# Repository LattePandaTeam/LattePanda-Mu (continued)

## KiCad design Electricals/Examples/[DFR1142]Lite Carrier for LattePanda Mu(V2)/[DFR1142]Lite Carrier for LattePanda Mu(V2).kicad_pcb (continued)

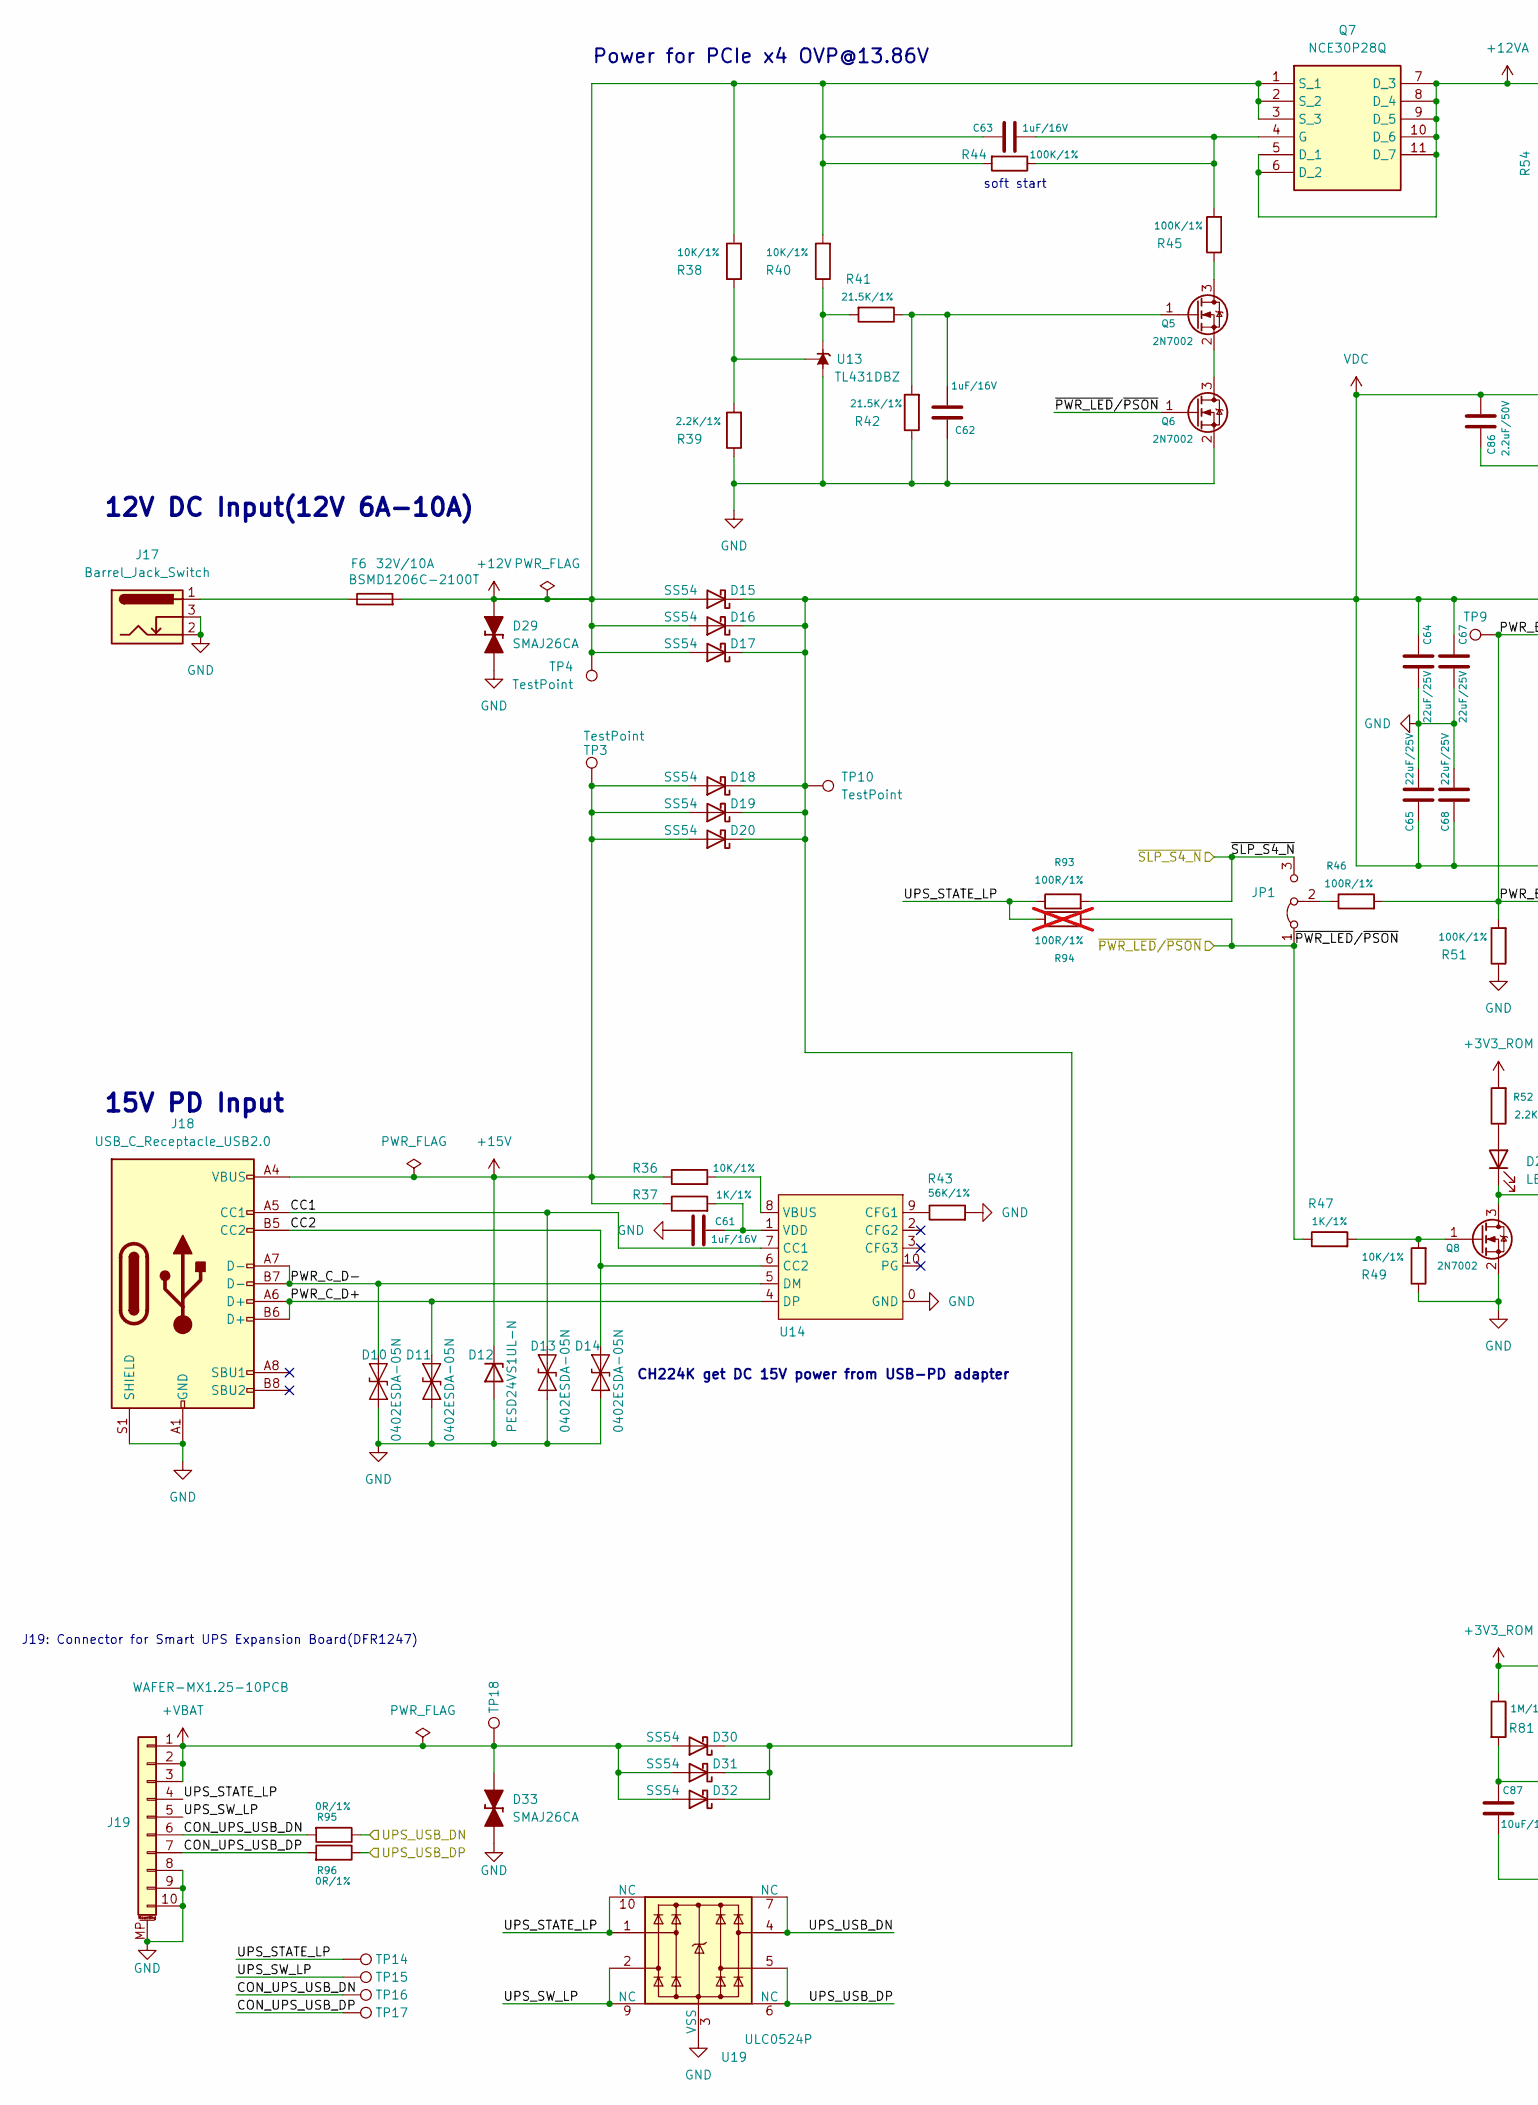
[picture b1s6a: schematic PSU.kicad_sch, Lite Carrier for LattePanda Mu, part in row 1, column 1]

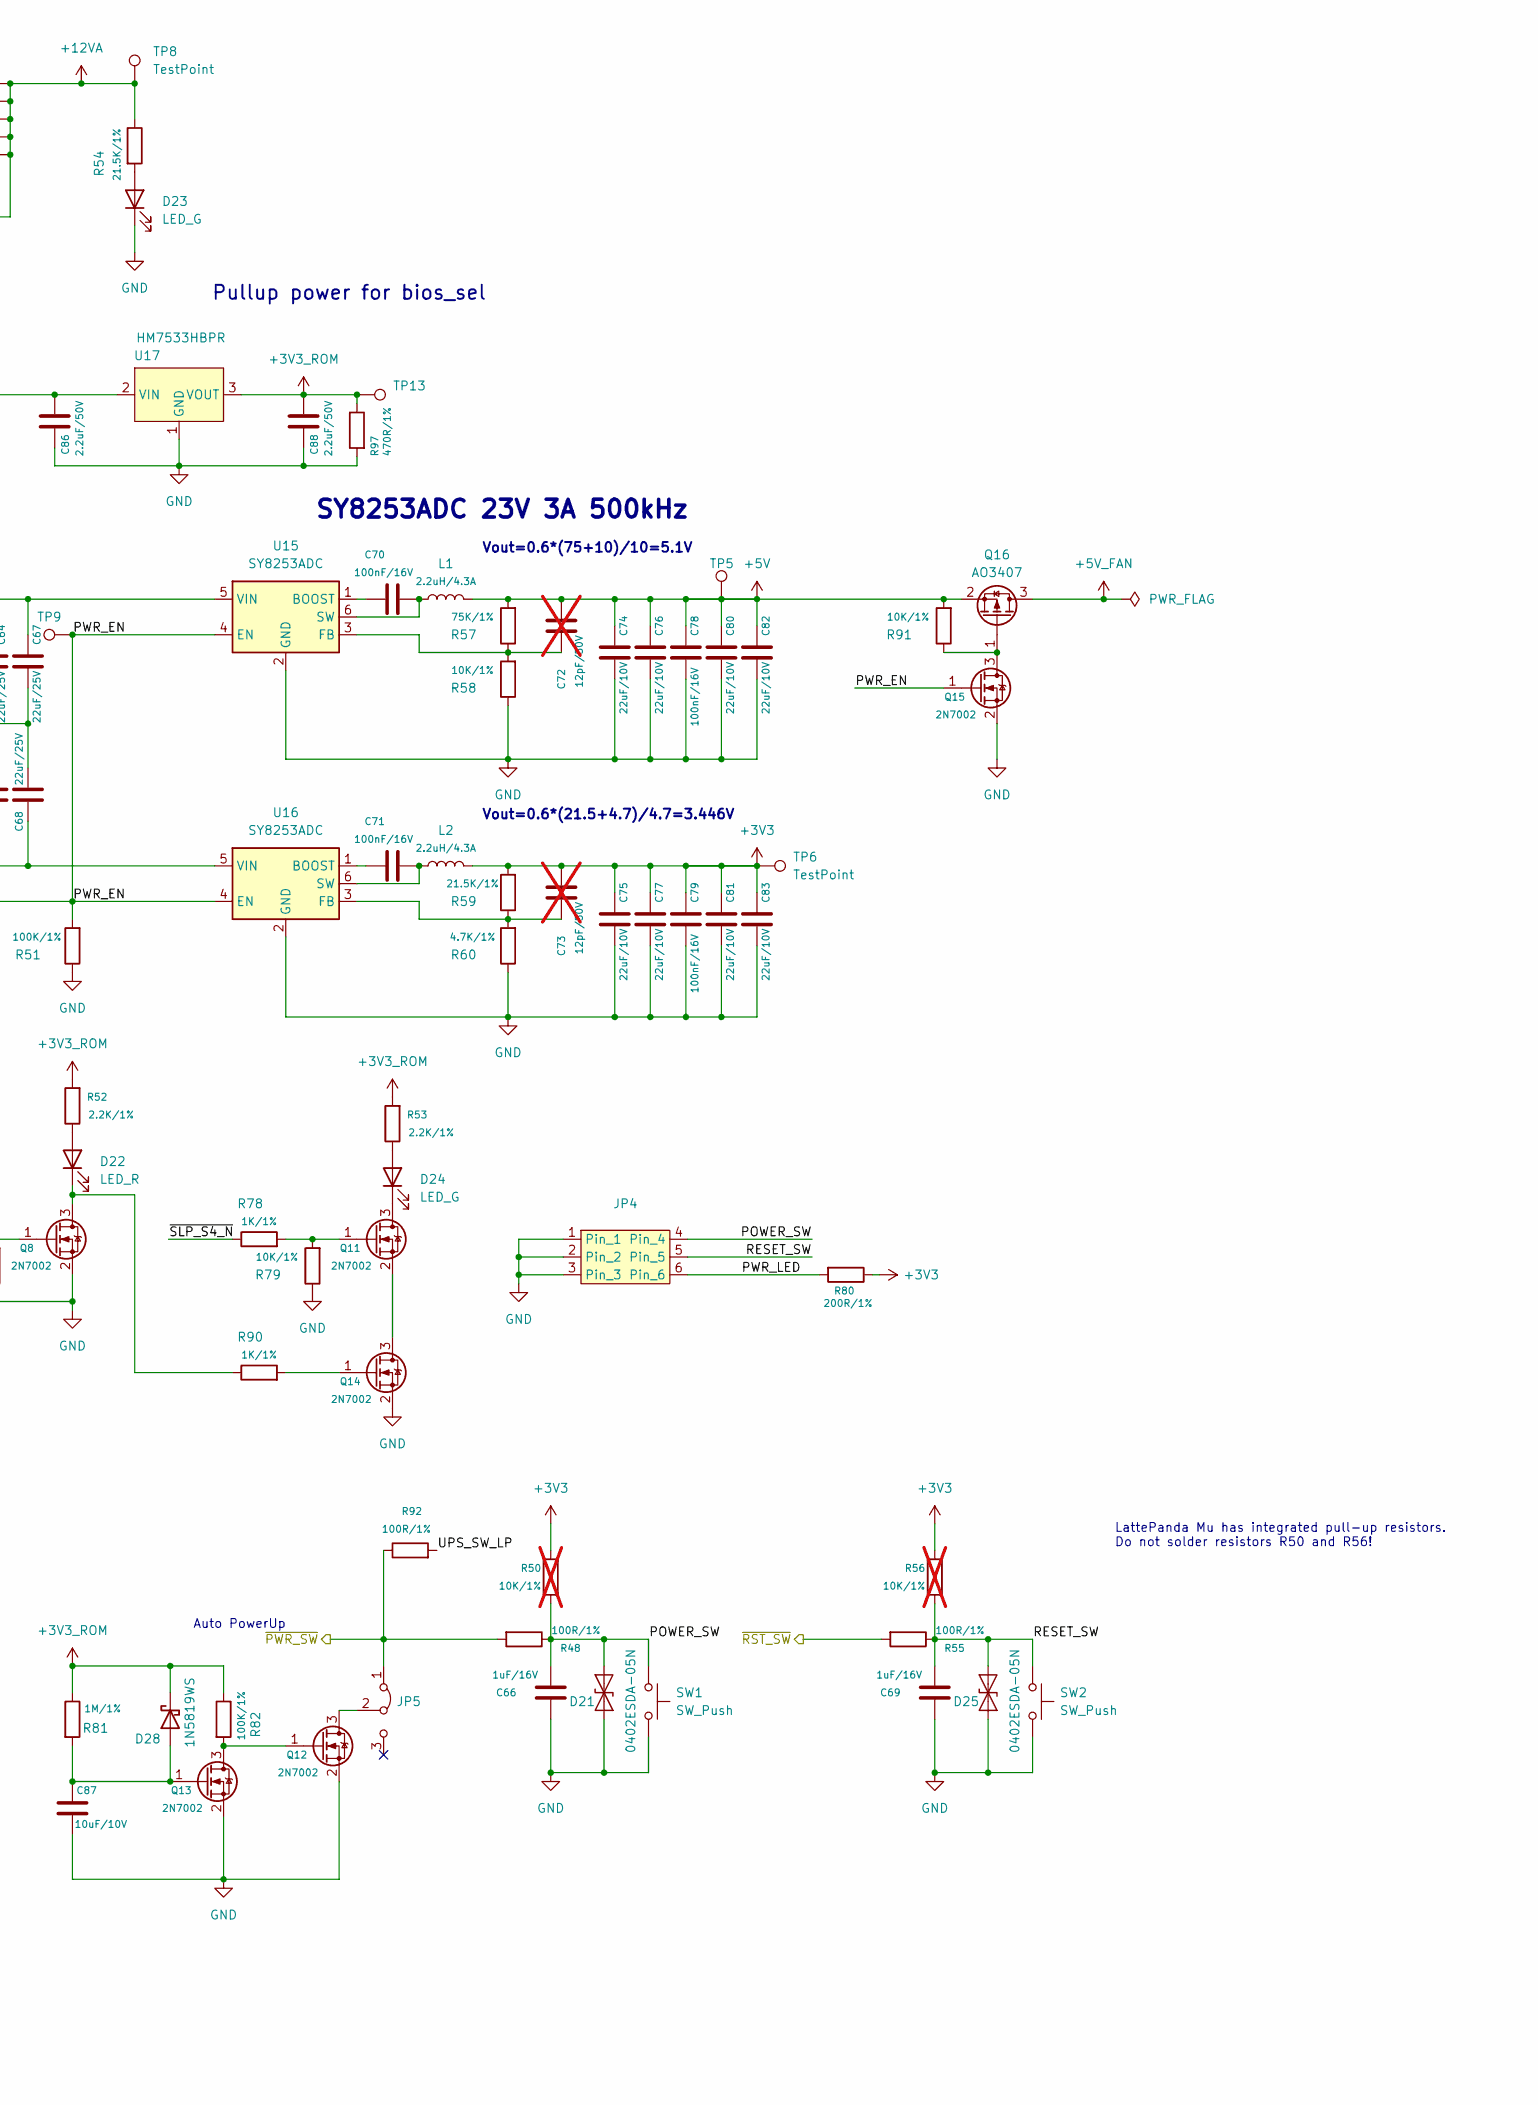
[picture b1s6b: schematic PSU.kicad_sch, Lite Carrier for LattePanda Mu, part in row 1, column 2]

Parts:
C61, C62, C63, C66, C69: 1uF/16V; C_0402_1005Metric
C64, C65, C67, C68: 22uF/25V; C_0805_2012Metric
C70, C71, C78, C79: 100nF/16V; C_0402_1005Metric
C72, C73: 12pF/50V; C_0402_1005Metric; not fitted
C74, C75, C76, C77, C80, C81, C82, C83: 22uF/10V; C_0603_1608Metric
C86, C88: 2.2uF/50V; C_0603
C87: 10uF/10V; C_0402_1005Metric
D10, D11, D13, D14, D21, D25: 0402ESDA-05N; D_0402_1005Metric
D12: PESD24VS1UL-N; D_0402_1005Metric
D15, D16, D17, D18, D19, D20, D30, D31, D32: SS54; D_SMA
D22: LED_R; LED_0603_1608Metric
D23, D24: LED_G; LED_0603_1608Metric
D28: 1N5819WS; D_SOD-323
D29, D33: SMAJ26CA; D_SMA
F6: BSMD1206C-2100T; R_1206
J17: Barrel_Jack_Switch; DC_Jack_DC007B_30V_10A
J18: USB_C_Receptacle_USB2.0; USB_C_Receptacle_G-Switch_GT-USB-7010ASV
J19: WAFER-MX1.25-10PCB; MX1.25-10P-SMD
JP1, JP5: Jumper_3_Bridged12; PinHeader_1x03_P2.54mm_Vertical
JP4: PinHeader_2x03_P2.54mm_Vertical
L1, L2: 2.2uH/4.3A; L_Sunlord_SWPA4020S
Q5, Q6, Q8, Q11, Q12, Q13, Q14, Q15: 2N7002; SOT-23
Q7: NCE30P28Q; MOSFET_PDFN8_3.3x3.3
Q16: AO3407; SOT-23
R36, R38, R40, R49, R58, R79, R91: 10K/1%; R_0402
R37, R47, R78, R90: 1K/1%; R_0402
R39, R52, R53: 2.2K/1%; R_0402
R41, R42, R54, R59: 21.5K/1%; R_0402
R43: 56K/1%; R_0402
R44, R45, R51, R82: 100K/1%; R_0402
R46, R48, R55, R92, R93: 100R/1%; R_0402
R50, R56: 10K/1%; R_0402_1005Metric; not fitted
R57: 75K/1%; R_0402
R60: 4.7K/1%; R_0402
R80: 200R/1%; R_0402
R81: 1M/1%; R_0402
R94: 100R/1%; R_0402; not fitted
R95, R96: 0R/1%; R_0402
R97: 470R/1%; R_0402
SW1, SW2: SW_Push; SW_PUSH_SIDE_TS-1012EV_7.7x3.95x3.5mm
TP3, TP4, TP5, TP6, TP8, TP9, TP10, TP13, TP14, TP15, TP16, TP17, TP18: TestPoint; TestPoint_Pad_D1.5mm
U13: TL431DBZ; SOT-23
U14: CH224K; ESSOP-10-1EP_3.9x5mm_P1.0mm_EP3.2x2.3
U15, U16: SY8253ADC; TSOT-23-6
U17: HM7533HBPR; SOT-89-3
U19: ULC0524P; Diodes_UDFN-10_1.0x2.5mm_P0.5mm

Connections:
+3V3: C73.1, C75.2, C77.2, C79.1, C81.2, C83.2, L2.2, R50.2, R56.2, R59.2, R80.1, TP6.1; also elsewhere on the board
+3V3_ROM: C88.1, D28.1 (K), R52.2, R53.2, R81.1, R82.1, R97.1, TP13.1, U17.3 (VOUT); also elsewhere on the board
+5V: C72.1, C74.2, C76.2, C78.1, C80.2, C82.2, L1.2, Q16.2 (S), R57.2, R91.2, TP5.1; also elsewhere on the board
+5V_FAN: Q16.3 (D); also elsewhere on the board
+12V: C63.2, D15.2 (A), D16.2 (A), D17.2 (A), D29.2 (A), F6.2, Q7.1 (S_1), Q7.2 (S_2), Q7.3 (S_3), R38.2, R40.2, R44.2, TP4.1
+12VA: Q7.5 (D_1), Q7.6 (D_2), Q7.7 (D_3), Q7.8 (D_4), Q7.9 (D_5), Q7.10 (D_6), Q7.11 (D_7), R54.1, TP8.1; also elsewhere on the board
+15V: D12.1 (K), D18.2 (A), D19.2 (A), D20.2 (A), J18.A4 (VBUS), J18.A9 (VBUS), J18.B4 (VBUS), J18.B9 (VBUS), R36.1, R37.1, TP3.1
+VBAT: D30.2 (A), D31.2 (A), D32.2 (A), D33.2 (A), J19.1, J19.2, J19.3, TP18.1
/LattePanda Module/~PWR_SW: JP5.1 (A), R48.2, R92.1; also elsewhere on the board
/LattePanda Module/~RST_SW: R55.2; also elsewhere on the board
/PSU/CC1: D13.2 (A2), J18.A5 (CC1), U14.7 (CC1)
/PSU/CC2: D14.2 (A2), J18.B5 (CC2), U14.6 (CC2)
/PSU/CON_UPS_USB_DN: J19.6, R95.2, TP16.1
/PSU/CON_UPS_USB_DP: J19.7, R96.2, TP17.1
/PSU/POWER_SW: C66.1, D21.2 (A2), JP4.4, R48.1, R50.1, SW1.1
/PSU/PWR_C_D+: D11.2 (A2), J18.A6 (D+), J18.B6 (D+), U14.4 (DP)
/PSU/PWR_C_D-: D10.2 (A2), J18.A7 (D-), J18.B7 (D-), U14.5 (DM)
/PSU/PWR_EN: Q15.1 (G), R46.2, R51.2, TP9.1, U15.4 (EN), U16.4 (EN)
/PSU/PWR_LED: JP4.6, R80.2
/PSU/RESET_SW: C69.1, D25.2 (A2), JP4.5, R55.1, R56.1, SW2.1
/PSU/UPS_STATE_LP: J19.4, R93.1, R94.1, TP14.1, U19.1, U19.10 (NC)
/PSU/UPS_SW_LP: J19.5, R92.2, TP15.1, U19.2, U19.9 (NC)
/PSU/UPS_USB_DN: R95.1; also elsewhere on the board
/PSU/UPS_USB_DP: R96.1; also elsewhere on the board
/PSU/~SLP_S4_N: JP1.3 (B), R78.1, R93.2; also elsewhere on the board
/~PWR_LED/~PSON: JP1.1 (A), Q6.1 (G), R47.1, R94.2; also elsewhere on the board
GND: C61.2, C62.2, C64.1, C65.1, C66.2, C67.1, C68.1, C69.2, C74.1, C75.1, C76.1, C77.1, C78.2, C79.2, C80.1, C81.1, C82.1, C83.1, C86.2, C87.2, C88.2, D10.1 (A1), D11.1 (A1), D12.2 (A), D13.1 (A1), D14.1 (A1), D21.1 (A1), D23.1 (K), D25.1 (A1), D29.1 (K), D33.1 (K), J17.2, J17.3, J18.A1 (GND), J18.A12 (GND), J18.B1 (GND), J18.B12 (GND), J18.S1 (SHIELD), J19.8, J19.9, J19.10, J19.MP (MountPin), JP4.1, JP4.2, JP4.3, Q6.2 (S), Q8.2 (S), Q12.2 (S), Q13.2 (S), Q14.2 (S), Q15.2 (S), R39.1, R42.1, R43.2, R49.1, R51.1, R58.1, R60.1, R79.1, R97.2, SW1.2, SW2.2, U13.3 (A), U14.0 (GND), U15.2 (GND), U16.2 (GND), U17.1 (GND), U19.3 (VSS), U19.8 (VSS); also elsewhere on the board
unnamed: D22.2 (A), R52.1
unnamed: D22.1 (K), Q8.3 (D), R90.1
unnamed: D23.2 (A), R54.2
unnamed: D24.2 (A), R53.1
unnamed: D24.1 (K), Q11.3 (D)
unnamed: C87.1, D28.2 (A), Q13.1 (G), R81.2
unnamed: F6.1, J17.1
unnamed: JP1.2 (C), R46.1
unnamed: JP5.2 (C), Q12.3 (D)
unnamed: Q5.3 (D), R45.1
unnamed: C62.1, Q5.1 (G), R41.1, R42.2
unnamed: Q5.2 (S), Q6.3 (D)
unnamed: C63.1, Q7.4 (G), R44.1, R45.2
unnamed: Q8.1 (G), R47.2, R49.2
unnamed: Q11.1 (G), R78.2, R79.2
unnamed: Q11.2 (S), Q14.3 (D)
unnamed: Q12.1 (G), Q13.3 (D), R82.2
unnamed: Q14.1 (G), R90.2
unnamed: Q15.3 (D), Q16.1 (G), R91.1
unnamed: R40.1, R41.2, U13.1 (K)
unnamed: R38.1, R39.2, U13.2 (REF)
unnamed: R43.1, U14.9 (CFG1)
unnamed: R36.2, U14.8 (VBUS)
unnamed: C61.1, R37.2, U14.1 (VDD)
unnamed: C70.2, U15.1 (BOOST)
unnamed: C72.2, R57.1, R58.2, U15.3 (FB)
unnamed: C70.1, L1.1, U15.6 (SW)
unnamed: C71.2, U16.1 (BOOST)
unnamed: C73.2, R59.1, R60.2, U16.3 (FB)
unnamed: C71.1, L2.1, U16.6 (SW)
unnamed: U19.4, U19.7 (NC)
unnamed: U19.5, U19.6 (NC)
VDC: C64.2, C65.2, C67.2, C68.2, C86.1, D15.1 (K), D16.1 (K), D17.1 (K), D18.1 (K), D19.1 (K), D20.1 (K), D30.1 (K), D31.1 (K), D32.1 (K), TP10.1, U15.5 (VIN), U16.5 (VIN), U17.2 (VIN); also elsewhere on the board

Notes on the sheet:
soft start
15V PD Input
J19: Connector for Smart UPS Expansion Board(DFR1247)
SY8253ADC 23V 3A 500kHz
Auto PowerUp
Power for PCIe x4 OVP@13.86V
Vout=0.6*(75+10)/10=5.1V
LattePanda Mu has integrated pull-up resistors. Do not solder resistors R50 and R56!
12V DC Input(12V 6A-10A)
CH224K get DC 15V power from USB-PD adapter
Pullup power for bios_sel
Vout=0.6*(21.5+4.7)/4.7=3.446V

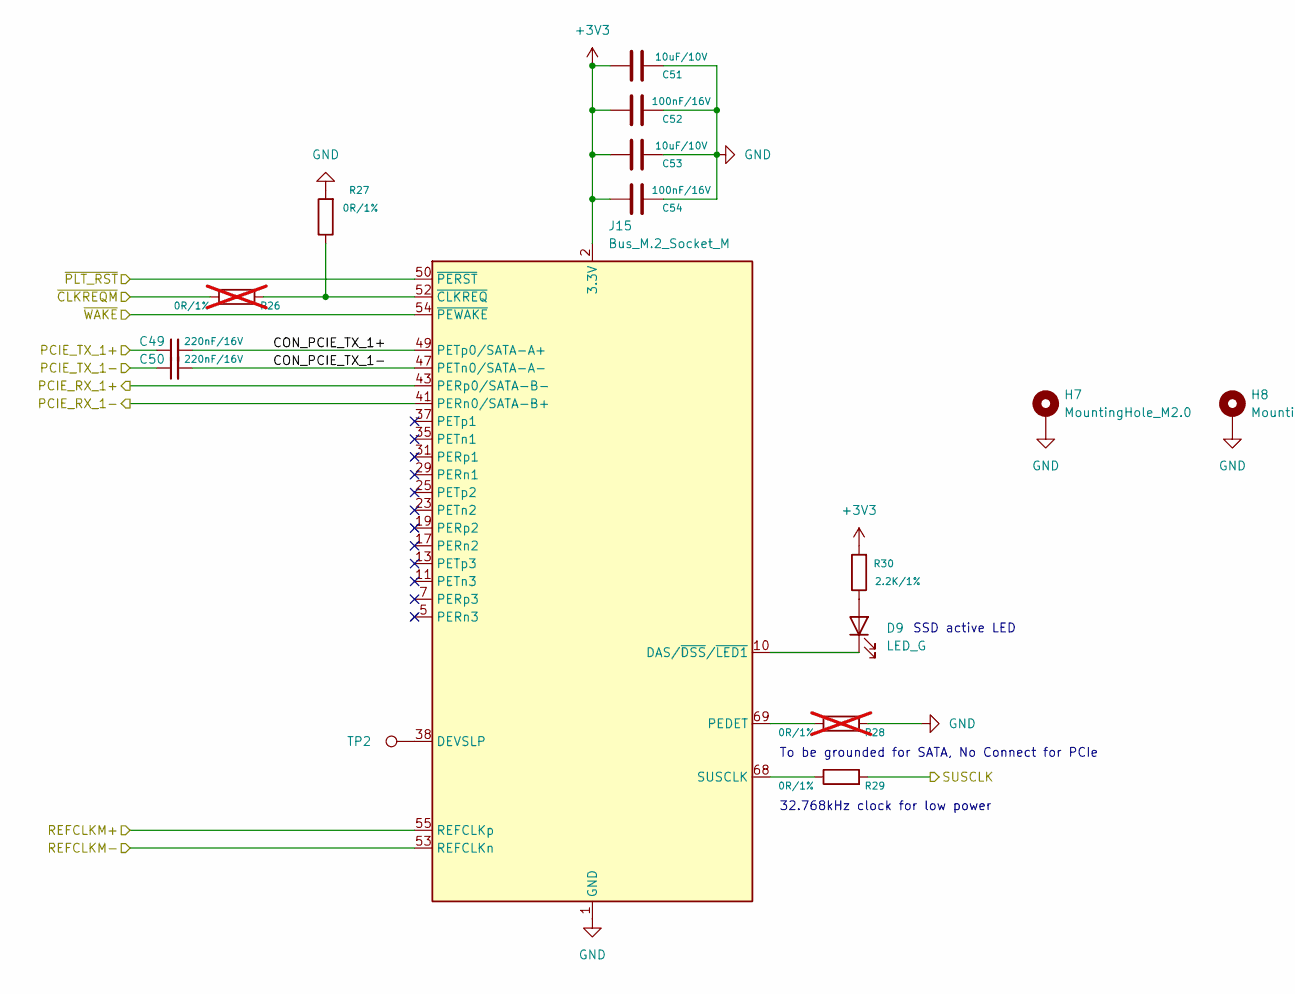
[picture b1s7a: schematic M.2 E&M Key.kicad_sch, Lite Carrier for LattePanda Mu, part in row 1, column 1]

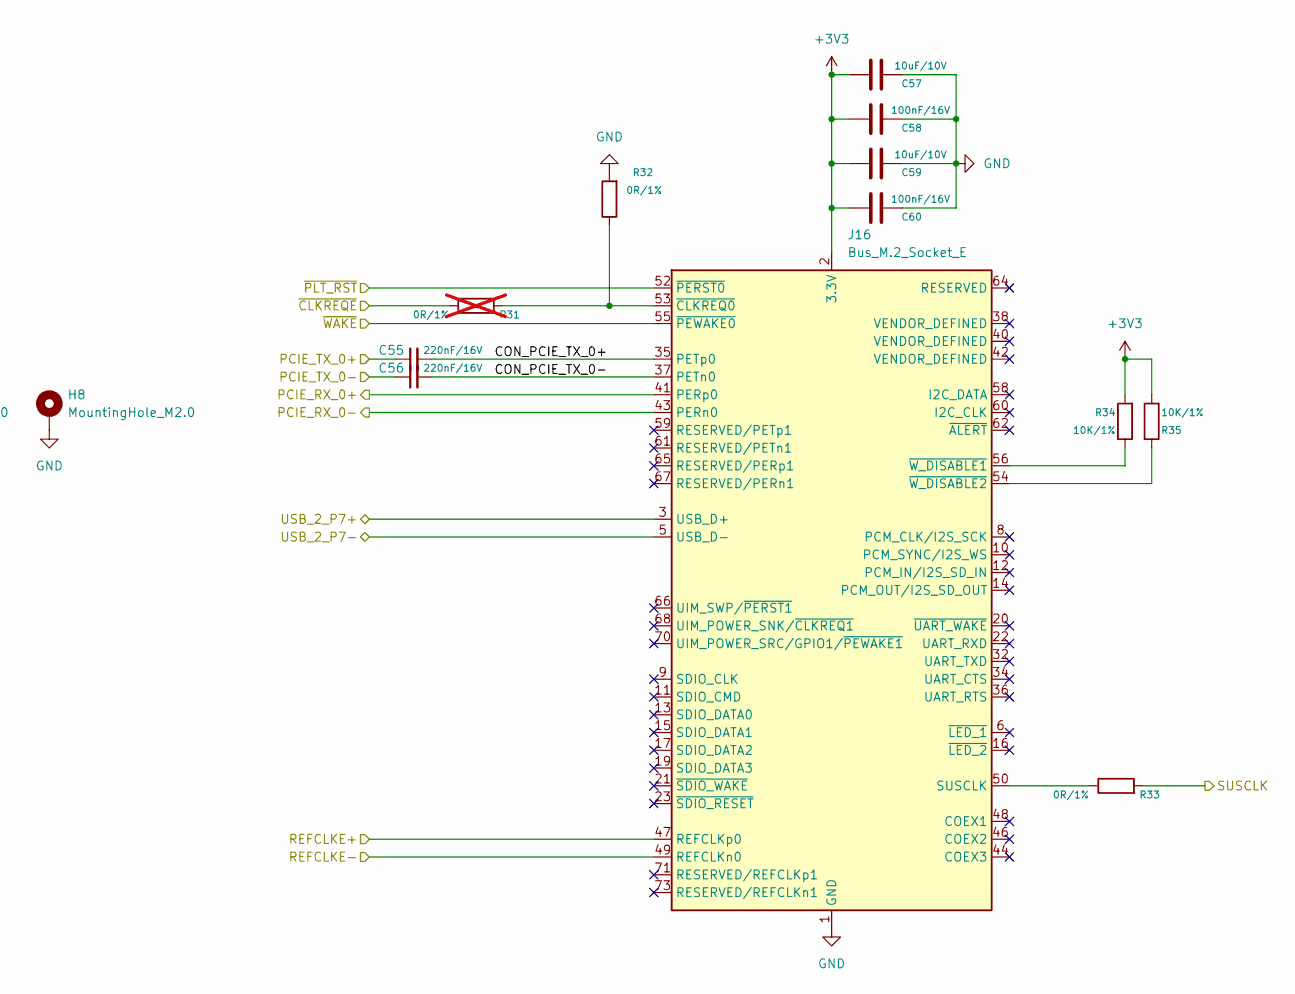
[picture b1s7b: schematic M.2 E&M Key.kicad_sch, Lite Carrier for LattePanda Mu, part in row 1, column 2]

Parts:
C49, C50, C55, C56: 220nF/16V; C_0402_1005Metric
C51, C53, C57, C59: 10uF/10V; C_0402_1005Metric
C52, C54, C58, C60: 100nF/16V; C_0402_1005Metric
D9: LED_G; LED_0603_1608Metric
H7, H8: MountingHole_M2.0; MountingHole_2.75mm_M2_4.4mm_Pad_TopOnly
J15: Bus_M.2_Socket_M; PCIe_M.2_Connectors_P=0.5mm_H=4.2mm_KeyM
J16: Bus_M.2_Socket_E; PCIe_M.2_Connectors_P=0.5mm_H=4.2mm_KeyE
R26, R28, R31: 0R/1%; R_0402_1005Metric; not fitted
R27, R29, R32, R33: 0R/1%; R_0402
R30: 2.2K/1%; R_0402
R34, R35: 10K/1%; R_0402
TP2: TestPoint; TestPoint_Pad_D1.5mm

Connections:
+3V3: C51.2, C52.2, C53.2, C54.2, C57.2, C58.2, C59.2, C60.2, J15.2 (3.3V), J15.4 (3.3V), J15.12 (3.3V), J15.14 (3.3V), J15.16 (3.3V), J15.18 (3.3V), J15.70 (3.3V), J15.72 (3.3V), J15.74 (3.3V), J16.2 (3.3V), J16.4 (3.3V), J16.72 (3.3V), J16.74 (3.3V), R30.2, R34.2, R35.1; also elsewhere on the board
/LattePanda Module/HSIO_2_RX+: J15.43 (PERp0/SATA-B-); also elsewhere on the board
/LattePanda Module/HSIO_2_RX-: J15.41 (PERn0/SATA-B+); also elsewhere on the board
/LattePanda Module/HSIO_2_TX+: C49.1; also elsewhere on the board
/LattePanda Module/HSIO_2_TX-: C50.1; also elsewhere on the board
/LattePanda Module/HSIO_3_RX+: J16.41 (PERp0); also elsewhere on the board
/LattePanda Module/HSIO_3_RX-: J16.43 (PERn0); also elsewhere on the board
/LattePanda Module/HSIO_3_TX+: C55.1; also elsewhere on the board
/LattePanda Module/HSIO_3_TX-: C56.1; also elsewhere on the board
/LattePanda Module/REFCLK0+: J15.53 (REFCLKn); also elsewhere on the board
/LattePanda Module/REFCLK0-: J15.55 (REFCLKp); also elsewhere on the board
/LattePanda Module/REFCLK3+: J16.47 (REFCLKp0); also elsewhere on the board
/LattePanda Module/REFCLK3-: J16.49 (REFCLKn0); also elsewhere on the board
/LattePanda Module/SUSCLK_WIFI: R29.2, R33.2; also elsewhere on the board
/LattePanda Module/USB_2_P7+: J16.3 (USB_D+); also elsewhere on the board
/LattePanda Module/USB_2_P7-: J16.5 (USB_D-); also elsewhere on the board
/LattePanda Module/~CLKREQ3: R31.1; also elsewhere on the board
/M.2 E&M Key/CON_PCIE_TX_0+: C55.2, J16.35 (PETp0)
/M.2 E&M Key/CON_PCIE_TX_0-: C56.2, J16.37 (PETn0)
/M.2 E&M Key/CON_PCIE_TX_1+: C49.2, J15.49 (PETp0/SATA-A+)
/M.2 E&M Key/CON_PCIE_TX_1-: C50.2, J15.47 (PETn0/SATA-A-)
/M.2 E&M Key/~CLKREQM: R26.1
/~PLT_RST: J15.50 (~PERST), J16.52 (~PERST0); also elsewhere on the board
/~WAKE: J15.54 (~PEWAKE), J16.55 (~PEWAKE0); also elsewhere on the board
GND: C51.1, C52.1, C53.1, C54.1, C57.1, C58.1, C59.1, C60.1, H7.1, H8.1, J15.1 (GND), J15.3 (GND), J15.9 (GND), J15.15 (GND), J15.21 (GND), J15.27 (GND), J15.33 (GND), J15.39 (GND), J15.45 (GND), J15.51 (GND), J15.57 (GND), J15.71 (GND), J15.73 (GND), J15.75 (GND), J15.MP1, J15.MP2, J16.1 (GND), J16.7 (GND), J16.18 (GND), J16.33 (GND), J16.39 (GND), J16.45 (GND), J16.51 (GND), J16.57 (GND), J16.63 (GND), J16.69 (GND), J16.75 (GND), J16.MP1, J16.MP2, R27.2, R28.2, R32.2; also elsewhere on the board
unnamed: D9.2 (A), R30.1
unnamed: D9.1 (K), J15.10 (DAS/~DSS/~LED1)
unnamed: J15.38 (DEVSLP), TP2.1
unnamed: J15.69 (PEDET), R28.1
unnamed: J15.68 (SUSCLK), R29.1
unnamed: J15.52 (~CLKREQ), R26.2, R27.1
unnamed: J16.50 (SUSCLK), R33.1
unnamed: J16.53 (~CLKREQ0), R31.2, R32.1
unnamed: J16.56 (~W_DISABLE1), R34.1
unnamed: J16.54 (~W_DISABLE2), R35.2

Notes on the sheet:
To be grounded for SATA, No Connect for PCIe
SSD active LED
32.768kHz clock for low power

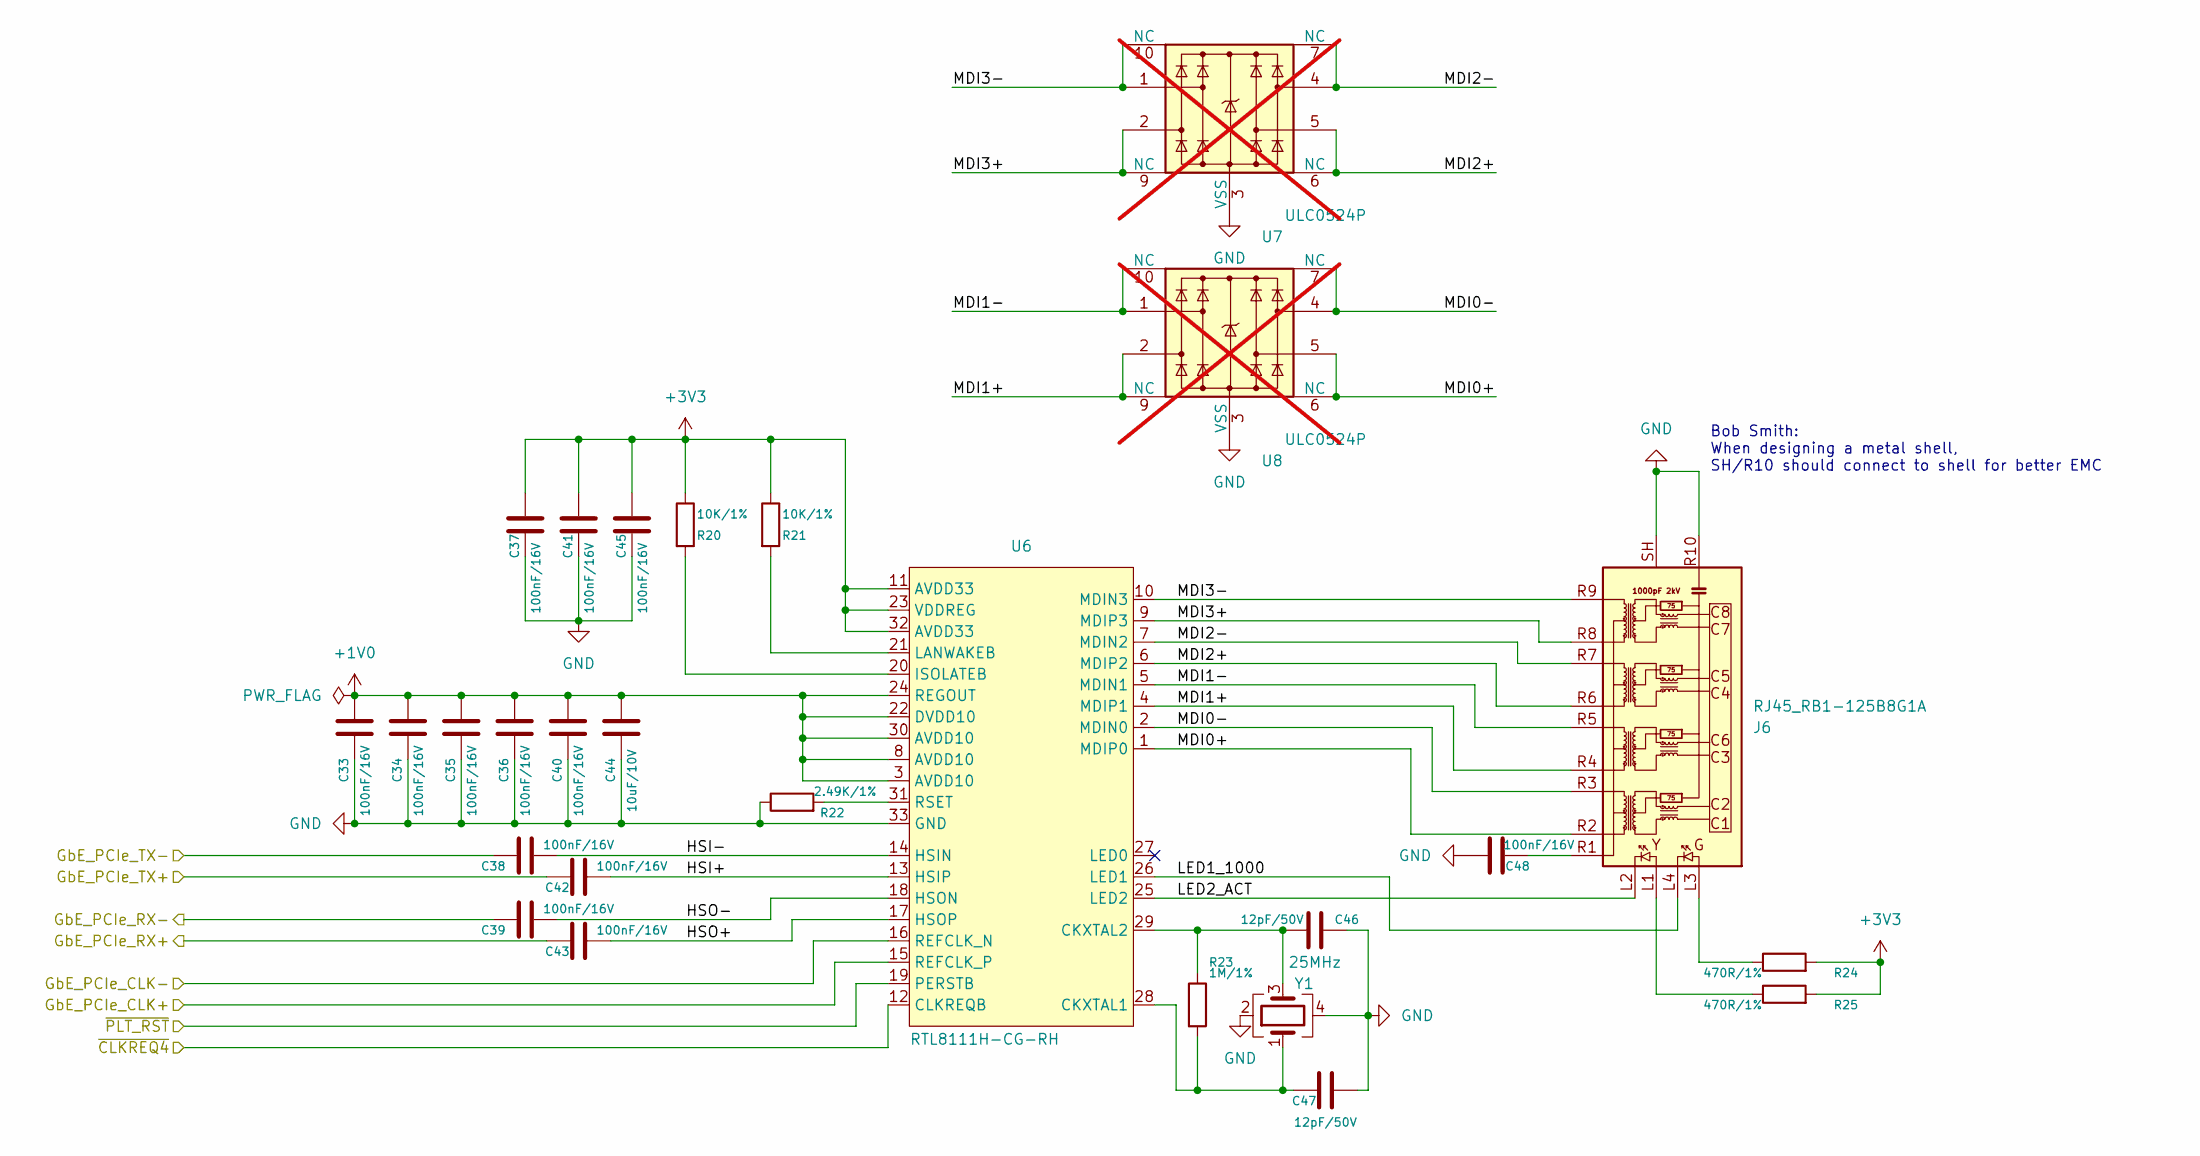
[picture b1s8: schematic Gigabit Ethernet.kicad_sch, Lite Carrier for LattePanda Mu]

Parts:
C33, C34, C35, C36, C37, C38, C39, C40, C41, C42, C43, C45, C48: 100nF/16V; C_0402_1005Metric
C44: 10uF/10V; C_0402_1005Metric
C46, C47: 12pF/50V; C_0402_1005Metric
J6: RJ45_RB1-125B8G1A; RJ45_UDE_RB1-125B8G1A
R20, R21: 10K/1%; R_0402
R22: 2.49K/1%; R_0603_1608Metric
R23: 1M/1%; R_0402
R24, R25: 470R/1%; R_0402
U6: RTL8111H-CG-RH; QFN-32-1EP_4x4mm_P0.4mm_EP2.65x2.65mm
U7, U8: ULC0524P; Diodes_UDFN-10_1.0x2.5mm_P0.5mm; not fitted
Y1: 25MHz; Crystal_SMD_3225-4Pin_3.2x2.5mm

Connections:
+1V0: C33.2, C34.2, C35.2, C36.2, C40.2, C44.2, U6.3 (AVDD10), U6.8 (AVDD10), U6.22 (DVDD10), U6.24 (REGOUT), U6.30 (AVDD10)
+3V3: C37.2, C41.2, C45.2, R20.1, R21.1, R24.2, R25.2, U6.11 (AVDD33), U6.23 (VDDREG), U6.32 (AVDD33); also elsewhere on the board
/Gigabit Ethernet/GbE_PCIe_CLK+: U6.15 (REFCLK_P); also elsewhere on the board
/Gigabit Ethernet/GbE_PCIe_CLK-: U6.16 (REFCLK_N); also elsewhere on the board
/Gigabit Ethernet/GbE_PCIe_RX+: C43.2; also elsewhere on the board
/Gigabit Ethernet/GbE_PCIe_RX-: C39.2; also elsewhere on the board
/Gigabit Ethernet/GbE_PCIe_TX+: C42.2; also elsewhere on the board
/Gigabit Ethernet/GbE_PCIe_TX-: C38.2; also elsewhere on the board
/Gigabit Ethernet/HSI+: C42.1, U6.13 (HSIP)
/Gigabit Ethernet/HSI-: C38.1, U6.14 (HSIN)
/Gigabit Ethernet/HSO+: C43.1, U6.17 (HSOP)
/Gigabit Ethernet/HSO-: C39.1, U6.18 (HSON)
/Gigabit Ethernet/LED0_100: U6.27 (LED0)
/Gigabit Ethernet/LED1_1000: J6.L4, U6.26 (LED1)
/Gigabit Ethernet/LED2_ACT: J6.L2, U6.25 (LED2)
/Gigabit Ethernet/MDI0+: J6.R2 (TD1+), U6.1 (MDIP0), U8.5, U8.6 (NC)
/Gigabit Ethernet/MDI0-: J6.R3 (TD1-), U6.2 (MDIN0), U8.4, U8.7 (NC)
/Gigabit Ethernet/MDI1+: J6.R4 (TD2+), U6.4 (MDIP1), U8.2, U8.9 (NC)
/Gigabit Ethernet/MDI1-: J6.R5 (TD2-), U6.5 (MDIN1), U8.1, U8.10 (NC)
/Gigabit Ethernet/MDI2+: J6.R6 (TD3+), U6.6 (MDIP2), U7.5, U7.6 (NC)
/Gigabit Ethernet/MDI2-: J6.R7 (TD3-), U6.7 (MDIN2), U7.4, U7.7 (NC)
/Gigabit Ethernet/MDI3+: J6.R8 (TD4+), U6.9 (MDIP3), U7.2, U7.9 (NC)
/Gigabit Ethernet/MDI3-: J6.R9 (TD4-), U6.10 (MDIN3), U7.1, U7.10 (NC)
/Gigabit Ethernet/~CLKREQ4: U6.12 (CLKREQB); also elsewhere on the board
/~PLT_RST: U6.19 (PERSTB); also elsewhere on the board
GND: C33.1, C34.1, C35.1, C36.1, C37.1, C40.1, C41.1, C44.1, C45.1, C46.1, C47.1, C48.2, J6.R10 (GND), J6.SH, R22.1, U6.33 (GND), U7.3 (VSS), U7.8 (VSS), U8.3 (VSS), U8.8 (VSS), Y1.2, Y1.4; also elsewhere on the board
unnamed: C48.1, J6.R1 (CT)
unnamed: J6.L1, R25.1
unnamed: J6.L3, R24.1
unnamed: C47.2, R23.2, U6.28 (CKXTAL1), Y1.1
unnamed: C46.2, R23.1, U6.29 (CKXTAL2), Y1.3
unnamed: R20.2, U6.20 (ISOLATEB)
unnamed: R21.2, U6.21 (LANWAKEB)
unnamed: R22.2, U6.31 (RSET)

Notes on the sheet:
Bob Smith: When designing a metal shell, SH/R10 should connect to shell for better EMC

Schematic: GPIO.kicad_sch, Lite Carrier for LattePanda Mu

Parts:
J7, J9, J12, J13: Conn_01x04_Pin; PinHeader_1x04_P2.54mm_Vertical
J8, J10, J11, J14: Conn_01x03_Pin; PinHeader_1x03_P2.54mm_Vertical
U9, U10, U11, U12: ULC0524P; Diodes_UDFN-10_1.0x2.5mm_P0.5mm

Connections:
+3V3: J13.1, J13.2, J13.3, J13.4, J14.1, J14.2, J14.3; also elsewhere on the board
/GPIO/I2C2_SCL: J9.1, U11.1, U11.10 (NC); also elsewhere on the board
/GPIO/I2C2_SDA: J7.1, U9.1, U9.10 (NC); also elsewhere on the board
/GPIO/I2C3_SCL: J9.2, U11.2, U11.9 (NC); also elsewhere on the board
/GPIO/I2C3_SDA: J7.2, U9.2, U9.9 (NC); also elsewhere on the board
/GPIO/I2C4_SCL: J9.3, U11.4, U11.7 (NC); also elsewhere on the board
/GPIO/I2C4_SDA: J7.3, U9.4, U9.7 (NC); also elsewhere on the board
/GPIO/I2C5_SCL: J9.4, U11.5, U11.6 (NC); also elsewhere on the board
/GPIO/I2C5_SDA: J7.4, U9.5, U9.6 (NC); also elsewhere on the board
/GPIO/SOC_UART0_RX: J8.1, U10.1, U10.10 (NC); also elsewhere on the board
/GPIO/SOC_UART0_TX: J10.1, U12.1, U12.10 (NC); also elsewhere on the board
/GPIO/SOC_UART1_RX: J8.2, U10.2, U10.9 (NC); also elsewhere on the board
/GPIO/SOC_UART1_TX: J10.2, U12.2, U12.9 (NC); also elsewhere on the board
/GPIO/SOC_UART2_RX: J8.3, U10.4, U10.7 (NC); also elsewhere on the board
/GPIO/SOC_UART2_TX: J10.3, U12.4, U12.7 (NC); also elsewhere on the board
GND: J11.1, J11.2, J11.3, J12.1, J12.2, J12.3, J12.4, U9.3 (VSS), U9.8 (VSS), U10.3 (VSS), U10.8 (VSS), U11.3 (VSS), U11.8 (VSS), U12.3 (VSS), U12.8 (VSS); also elsewhere on the board
unnamed: U10.5, U10.6 (NC)
unnamed: U12.5, U12.6 (NC)

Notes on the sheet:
I2C have internal 2.2k resistor pull-up to 3V3 on LattePanda Mu compute module.

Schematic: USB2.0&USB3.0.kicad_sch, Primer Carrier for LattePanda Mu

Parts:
C26, C27, C28, C29: 100nF/16V; C_0402_1005Metric
C30, C31, C32: 22uF/10V; C_0603_1608Metric
D5, D6, D7, D8: 0402ESDA-05N; D_0402_1005Metric
F2, F3: 6V/1A; Fuse_0805_2012Metric
F4, F5: 6V/2A; Fuse_0805_2012Metric
J4: USB3_A_Stacked; USB3_A_Molex_48406-0001_Horizontal_Stacked
J5: USB_A_Stacked; USB_A_CUI_UJ2-ADH-TH_Horizontal_Stacked
U3, U4, U5: ULC0524P; Diodes_UDFN-10_1.0x2.5mm_P0.5mm

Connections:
+5V: C30.2, C31.2, C32.2, F2.1, F3.1, F4.1, F5.1; also elsewhere on the board
/LattePanda Module/HSIO_0_TX+: C27.1; also elsewhere on the board
/LattePanda Module/HSIO_0_TX-: C26.1; also elsewhere on the board
/LattePanda Module/HSIO_1_TX+: C29.1; also elsewhere on the board
/LattePanda Module/HSIO_1_TX-: C28.1; also elsewhere on the board
/USB2.0&USB3.0/CON_USB1_D_N: J5.2 (D1-), U4.2, U4.9 (NC); also elsewhere on the board
/USB2.0&USB3.0/CON_USB1_D_P: J5.3 (D1+), U4.1, U4.10 (NC); also elsewhere on the board
/USB2.0&USB3.0/CON_USB2_D_N: J5.6 (D2-), U4.5, U4.6 (NC); also elsewhere on the board
/USB2.0&USB3.0/CON_USB2_D_P: J5.7 (D2+), U4.4, U4.7 (NC); also elsewhere on the board
/USB2.0&USB3.0/CON_USB3_D_N: D8.2 (A2), J4.2 (D1-); also elsewhere on the board
/USB2.0&USB3.0/CON_USB3_D_P: D7.2 (A2), J4.3 (D1+); also elsewhere on the board
/USB2.0&USB3.0/CON_USB3_SSRX_N: J4.5 (SSRX1-), U5.4, U5.7 (NC); also elsewhere on the board
/USB2.0&USB3.0/CON_USB3_SSRX_P: J4.6 (SSRX1+), U5.5, U5.6 (NC); also elsewhere on the board
/USB2.0&USB3.0/CON_USB3_SSTX_N: C26.2, J4.8 (SSTX1-), U3.4, U3.7 (NC)
/USB2.0&USB3.0/CON_USB3_SSTX_P: C27.2, J4.9 (SSTX1+), U3.5, U3.6 (NC)
/USB2.0&USB3.0/CON_USB4_D_N: D6.2 (A2), J4.11 (D2-); also elsewhere on the board
/USB2.0&USB3.0/CON_USB4_D_P: D5.2 (A2), J4.12 (D2+); also elsewhere on the board
/USB2.0&USB3.0/CON_USB4_SSRX_N: J4.14 (SSRX2-), U5.1, U5.10 (NC); also elsewhere on the board
/USB2.0&USB3.0/CON_USB4_SSRX_P: J4.15 (SSRX2+), U5.2, U5.9 (NC); also elsewhere on the board
/USB2.0&USB3.0/CON_USB4_SSTX_N: C28.2, J4.17 (SSTX2-), U3.1, U3.10 (NC)
/USB2.0&USB3.0/CON_USB4_SSTX_P: C29.2, J4.18 (SSTX2+), U3.2, U3.9 (NC)
GND: C30.1, C31.1, C32.1, D5.1 (A1), D6.1 (A1), D7.1 (A1), D8.1 (A1), J4.4 (GND1), J4.7 (DRAIN1), J4.13 (GND2), J4.16 (DRAIN2), J4.19 (SHIELD), J5.4 (GND1), J5.8 (GND2), J5.9 (Shield), U3.3 (VSS), U3.8 (VSS), U4.3 (VSS), U4.8 (VSS), U5.3 (VSS), U5.8 (VSS); also elsewhere on the board
unnamed: F4.2, J4.1 (VBUS1)
unnamed: F5.2, J4.10 (VBUS2)
unnamed: F2.2, J5.1 (VBUS1)
unnamed: F3.2, J5.5 (VBUS2)
